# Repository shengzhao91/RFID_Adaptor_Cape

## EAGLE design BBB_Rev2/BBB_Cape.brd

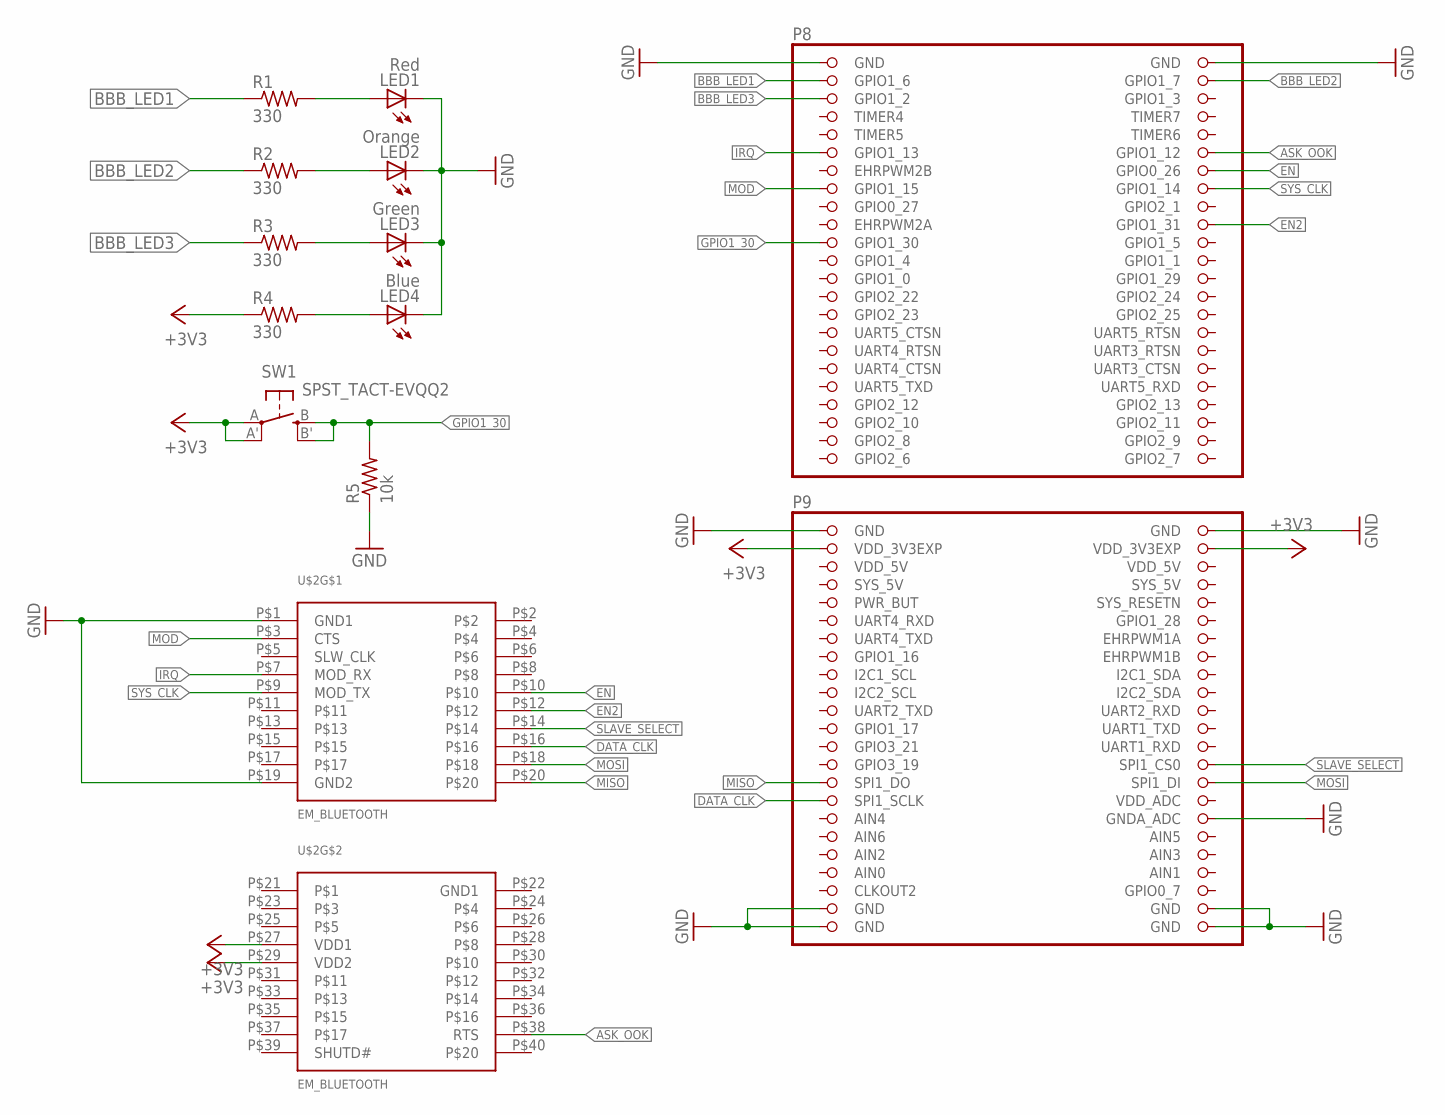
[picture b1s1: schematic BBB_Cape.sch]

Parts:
LED1: Red; CHIPLED_0805; MPN KPT-2012SECK-J3
LED2: Orange; CHIPLED_0805; MPN KP-2012SECK
LED3: Green; CHIPLED_0805; MPN KP-2012CGCK
LED4: Blue; CHIPLED_0805; MPN KPHBM-2012PBASURKC
R1, R2, R3, R4: 330; R0805; MPN CR0603-JW-331ELF
R5: 10k; R0805; MPN CRCW080510K0FKTA
SW1: SPST_TACT-EVQQ2; EVQ-Q2
U$1: BEAGLEBONE_OUTLINE; BEAGLEBONE_SHIELD
U$2: EM_BLUETOOTH; EM

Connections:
+3V3: R4.1, SW1.A, SW1.A' (P1), U$1.49 (VDD_3V3EXP), U$1.50 (VDD_3V3EXP), U$2.P$27 (VDD1), U$2.P$29 (VDD2)
AIN0: U$1.85 (AIN0)
ASK_OOK: U$1.12 (GPIO1_12), U$2.P$38 (RTS)
BBB_LED1: R1.1, U$1.3 (GPIO1_6)
BBB_LED2: R2.1, U$1.4 (GPIO1_7)
BBB_LED3: R3.1, U$1.5 (GPIO1_2)
DATA_CLK: U$1.77 (SPI1_SCLK), U$2.P$16
EN: U$1.14 (GPIO0_26), U$2.P$10
EN2: U$1.20 (GPIO1_31), U$2.P$12
GND: LED1.C, LED2.C, LED3.C, LED4.C, R5.1, U$1.1 (GND), U$1.2 (GND), U$1.47 (GND), U$1.48 (GND), U$1.80 (GNDA_ADC), U$1.89 (GND), U$1.90 (GND), U$1.91 (GND), U$1.92 (GND), U$2.P$1 (GND1), U$2.P$19 (GND2)
GPIO1_30: R5.2, SW1.B (S), SW1.B' (S1), U$1.21 (GPIO1_30)
IRQ: U$1.11 (GPIO1_13), U$2.P$7 (MOD_RX)
MISO: U$1.75 (SPI1_DO), U$2.P$20
MOD: U$1.15 (GPIO1_15), U$2.P$3 (CTS)
MOSI: U$1.76 (SPI1_DI), U$2.P$18
unnamed: LED1.A, R1.2
unnamed: LED2.A, R2.2
unnamed: LED3.A, R3.2
unnamed: LED4.A, R4.2
SLAVE_SELECT: U$1.74 (SPI1_CS0), U$2.P$14
SYS_5V: U$1.53 (SYS_5V)
SYS_CLK: U$1.16 (GPIO1_14), U$2.P$9 (MOD_TX)
VDD_5V: U$1.51 (VDD_5V), U$1.52 (VDD_5V)

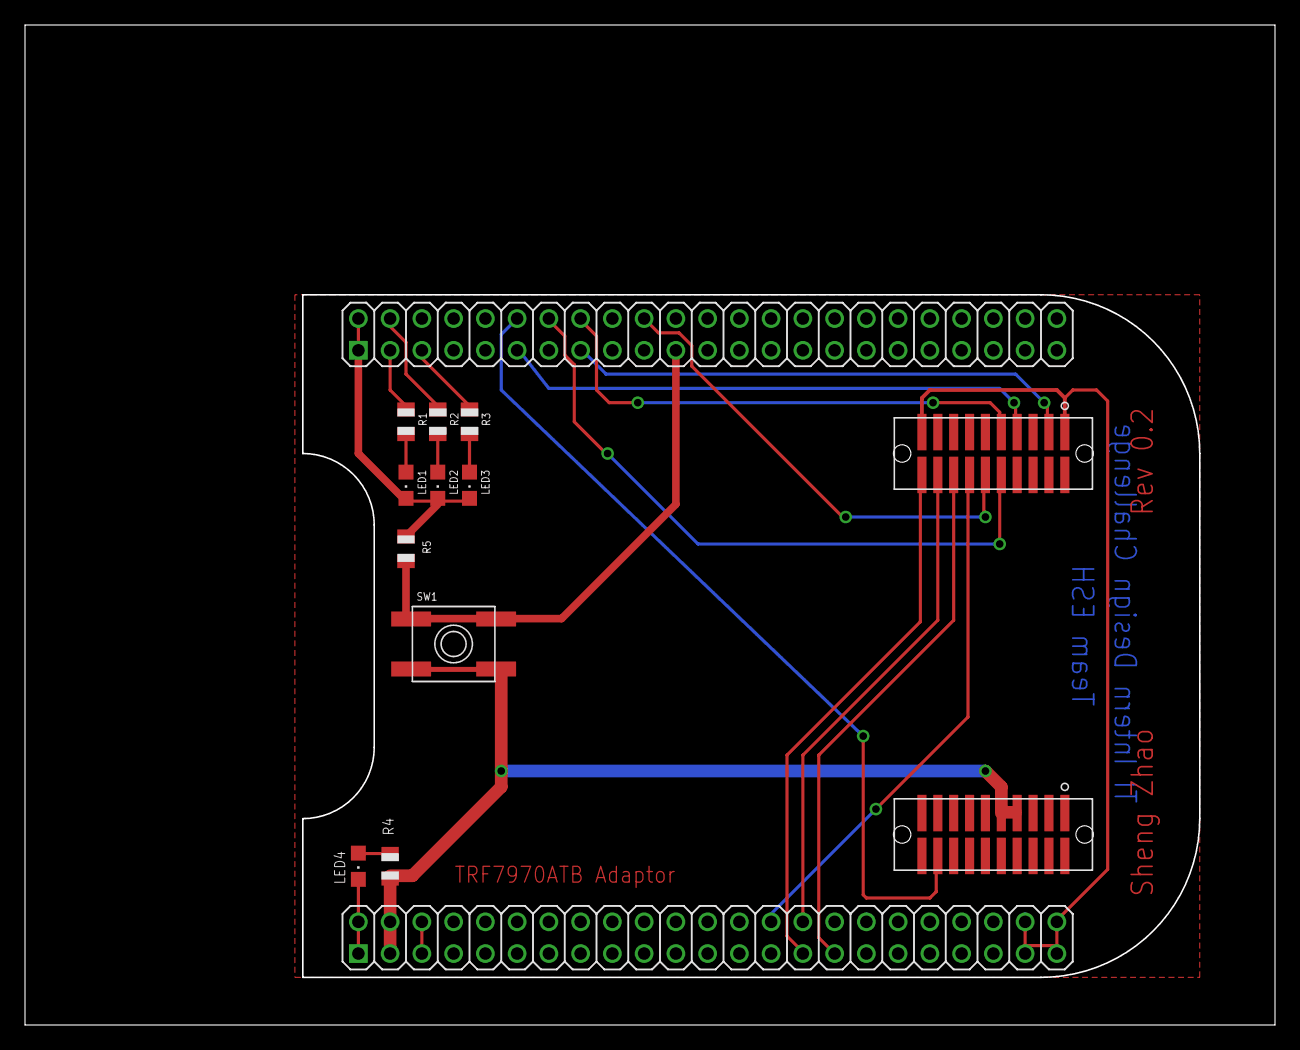
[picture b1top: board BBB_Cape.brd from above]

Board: 2 copper layers, 100.0 x 80.0 mm, 12 parts (0 on the bottom side), 21 nets.

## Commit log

2013-07-26 Added RFID Application and SPI device tree
2013-07-26 Cape Schematic, Layout, and Gerber
2013-07-26 updated Cape schematic, added BOM
2013-07-26 Video Streaming code
2013-07-29 minor cleaned up for basic RFID UID reading.
2013-07-30 Added automatic SPI Device tree enable and unlockDemo.c
2013-08-02 minor syntax edit
